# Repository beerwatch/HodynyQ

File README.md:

# HodynyQ
RP2040 to replace RPi Linux in my desktop alarm clock and enable functionality extension towards wearable watch

# Note about Google Oauth2 application identity key
The Oauth2/client_secret.json file contains Google Oauth2 application identity. It is used to present application information and security policies and for tracking application use. A personified access token is needed to actually access Google API. 
The access token is generated during process that involves actual person's log-in. The resulting access token file shall be uploaded as Oauth2/client_token.json.

For more information see https://developers.google.com/identity/protocols/oauth2. Because of limitations listed in https://developers.google.com/identity/protocols/oauth2/limited-input-device#allowedscopes I had to use https://developers.google.com/identity/protocols/oauth2/native-app. I don't really understand why there is such limitation when your application wants only to read calendar items as they can be shared to anybody by the user.

The application components around SGApi.py showcase minimal Micropython code to interact with Google Oauth2 that leaves some of RP2040 RAM free to run other tasks. Oops, I did it again!

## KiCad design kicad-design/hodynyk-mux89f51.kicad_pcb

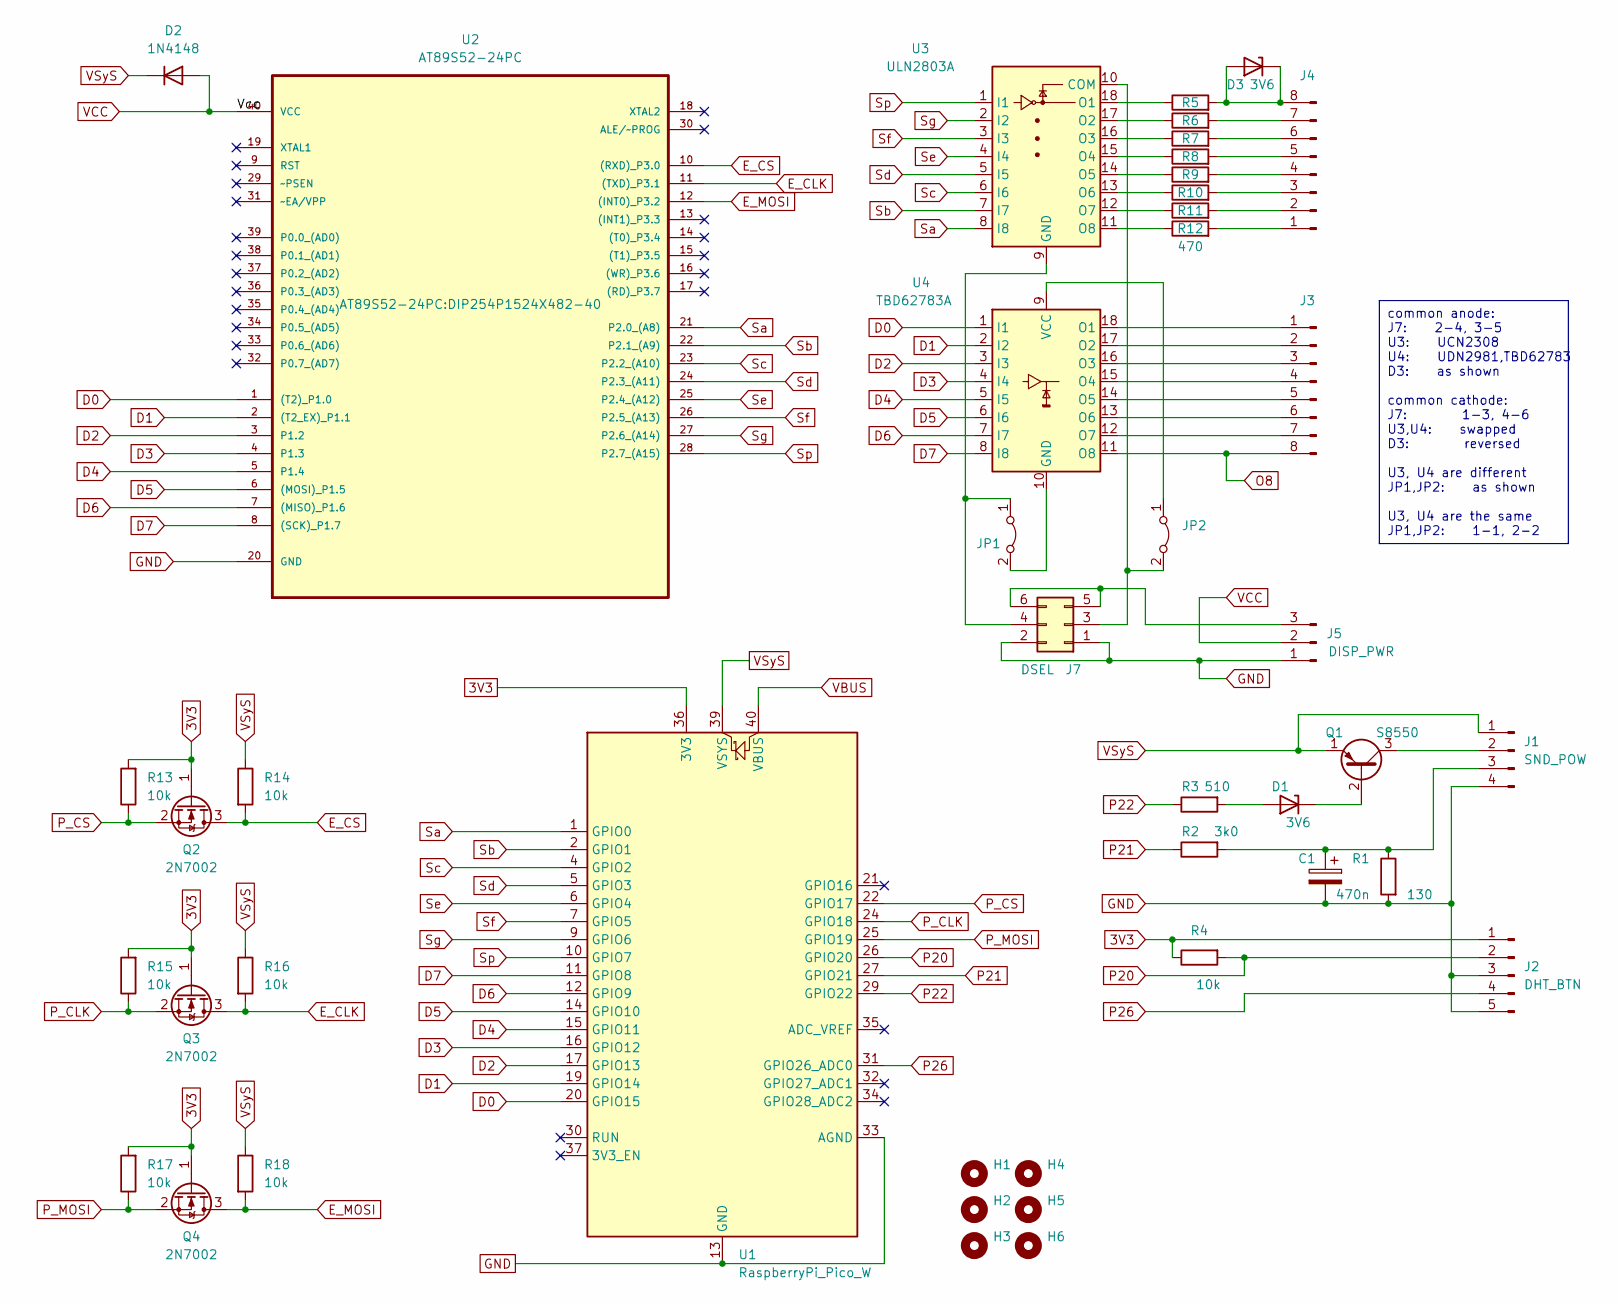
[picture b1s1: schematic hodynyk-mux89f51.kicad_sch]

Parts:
C1: 470n; CP_Radial_D4.0mm_P2.00mm
D1: 3V6; D_DO-35_SOD27_P7.62mm_Horizontal
D2: 1N4148; D_DO-35_SOD27_P7.62mm_Horizontal
D3: 3V6; D_DO-34_SOD68_P7.62mm_Horizontal
H1, H2, H3, H4, H5, H6: MountingHole_2.2mm_M2_ISO14580
J1: SND_POW; PinHeader_1x04_P2.54mm_Vertical
J2: DHT_BTN; PinHeader_1x05_P2.54mm_Vertical
J3: DISP_D; PinHeader_1x08_P2.54mm_Vertical
J4: DISP_S; PinHeader_1x08_P2.54mm_Vertical
J5: DISP_PWR; PinHeader_1x03_P2.54mm_Vertical
J7: DSEL; PinHeader_2x03_P2.54mm_Vertical
JP1, JP2: Jumper_2_Bridged; SolderJumper-2_P1.3mm_Bridged_Pad1.0x1.5mm
Q1: S8550; TO-92_HandSolder
Q2, Q3, Q4: 2N7002; SOT-23
R1: 130; R_Axial_DIN0204_L3.6mm_D1.6mm_P7.62mm_Horizontal
R2: 3k0; R_Axial_DIN0204_L3.6mm_D1.6mm_P7.62mm_Horizontal
R3: 510; R_Axial_DIN0204_L3.6mm_D1.6mm_P7.62mm_Horizontal
R4: 10k; R_Axial_DIN0204_L3.6mm_D1.6mm_P7.62mm_Horizontal
R5, R6, R7, R8, R9, R10, R11, R12: 470; R_Axial_DIN0204_L3.6mm_D1.6mm_P7.62mm_Horizontal
R13, R14, R15, R16, R17, R18: 10k; R_0603_1608Metric
U1: RaspberryPi_Pico_W; RaspberryPi_Pico_Common
U2: AT89S52-24PC; DIP254P1524X482-40; MPN AT89S52-24PC
U3: ULN2803A; DIP-18_W7.62mm_Socket_LongPads
U4: TBD62783A; DIP-18_W7.62mm_Socket_LongPads

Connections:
3V3: J2.1, Q2.1 (G), Q3.1 (G), Q4.1 (G), R4.1, R13.2, R15.2, R17.2, U1.36 (3V3)
D0: U1.20 (GPIO15), U2.1 ((T2)_P1.0), U4.1 (I1)
D1: U1.19 (GPIO14), U2.2 ((T2_EX)_P1.1), U4.2 (I2)
D2: U1.17 (GPIO13), U2.3 (P1.2), U4.3 (I3)
D3: U1.16 (GPIO12), U2.4 (P1.3), U4.4 (I4)
D4: U1.15 (GPIO11), U2.5 (P1.4), U4.5 (I5)
D5: U1.14 (GPIO10), U2.6 ((MOSI)_P1.5), U4.6 (I6)
D6: U1.12 (GPIO9), U2.7 ((MISO)_P1.6), U4.7 (I7)
D7: U1.11 (GPIO8), U2.8 ((SCK)_P1.7), U4.8 (I8)
E_CLK: Q3.3 (D), R16.2, U2.11 ((TXD)_P3.1)
E_CS: Q2.3 (D), R14.2, U2.10 ((RXD)_P3.0)
E_MOSI: Q4.3 (D), R18.2, U2.12 ((INT0)_P3.2)
GND: C1.2, J1.4, J2.3, J2.5, J5.1, J7.1, J7.2, R1.2, U1.3 (GND), U1.8 (GND), U1.13 (GND), U1.18 (GND), U1.23 (GND), U1.28 (GND), U1.33 (AGND), U1.38 (GND), U2.20 (GND)
unnamed: D1.2 (A), R3.2
unnamed: D1.1 (K), Q1.2 (B)
unnamed: D3.1 (K), D3.2 (A), J4.8, R5.2
unnamed: J1.2, Q1.3 (C)
unnamed: C1.1, J1.3, R1.1, R2.2
unnamed: J3.1, U4.18 (O1)
unnamed: J3.2, U4.17 (O2)
unnamed: J3.3, U4.16 (O3)
unnamed: J3.4, U4.15 (O4)
unnamed: J3.5, U4.14 (O5)
unnamed: J3.6, U4.13 (O6)
unnamed: J3.7, U4.12 (O7)
unnamed: J4.1, R12.2
unnamed: J4.2, R11.2
unnamed: J4.3, R10.2
unnamed: J4.4, R9.2
unnamed: J4.5, R8.2
unnamed: J4.6, R7.2
unnamed: J4.7, R6.2
unnamed: J5.3, J7.5, J7.6
unnamed: J7.3, JP2.2 (B), U3.10 (COM)
unnamed: J7.4, JP1.1 (A), U3.9 (GND)
unnamed: JP1.2 (B), U4.10 (GND)
unnamed: JP2.1 (A), U4.9 (VCC)
unnamed: R5.1, U3.18 (O1)
unnamed: R6.1, U3.17 (O2)
unnamed: R7.1, U3.16 (O3)
unnamed: R8.1, U3.15 (O4)
unnamed: R9.1, U3.14 (O5)
unnamed: R10.1, U3.13 (O6)
unnamed: R11.1, U3.12 (O7)
unnamed: R12.1, U3.11 (O8)
O8: J3.8, U4.11 (O8)
P20: J2.2, R4.2, U1.26 (GPIO20)
P21: R2.1, U1.27 (GPIO21)
P22: R3.1, U1.29 (GPIO22)
P26: J2.4, U1.31 (GPIO26_ADC0)
P_CLK: Q3.2 (S), R15.1, U1.24 (GPIO18)
P_CS: Q2.2 (S), R13.1, U1.22 (GPIO17)
P_MOSI: Q4.2 (S), R17.1, U1.25 (GPIO19)
Sa: U1.1 (GPIO0), U2.21 (P2.0_(A8)), U3.8 (I8)
Sb: U1.2 (GPIO1), U2.22 (P2.1_(A9)), U3.7 (I7)
Sc: U1.4 (GPIO2), U2.23 (P2.2_(A10)), U3.6 (I6)
Sd: U1.5 (GPIO3), U2.24 (P2.3_(A11)), U3.5 (I5)
Se: U1.6 (GPIO4), U2.25 (P2.4_(A12)), U3.4 (I4)
Sf: U1.7 (GPIO5), U2.26 (P2.5_(A13)), U3.3 (I3)
Sg: U1.9 (GPIO6), U2.27 (P2.6_(A14)), U3.2 (I2)
Sp: U1.10 (GPIO7), U2.28 (P2.7_(A15)), U3.1 (I1)
VBUS: U1.40 (VBUS)
VCC: D2.2 (A), J5.2, U2.40 (VCC)
VSyS: D2.1 (K), J1.1, Q1.1 (E), R14.1, R16.1, R18.1, U1.39 (VSYS)

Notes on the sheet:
common anode: J7: 2-4, 3-5 U3: UCN2308 U4: UDN2981,TBD62783 D3: as shown common cathode: J7: 1-3, 4-6 U3,U4: swapped D3: reversed U3, U4 are different JP1,JP2: as shown U3, U4 are the same JP1,JP2: 1-1, 2-2

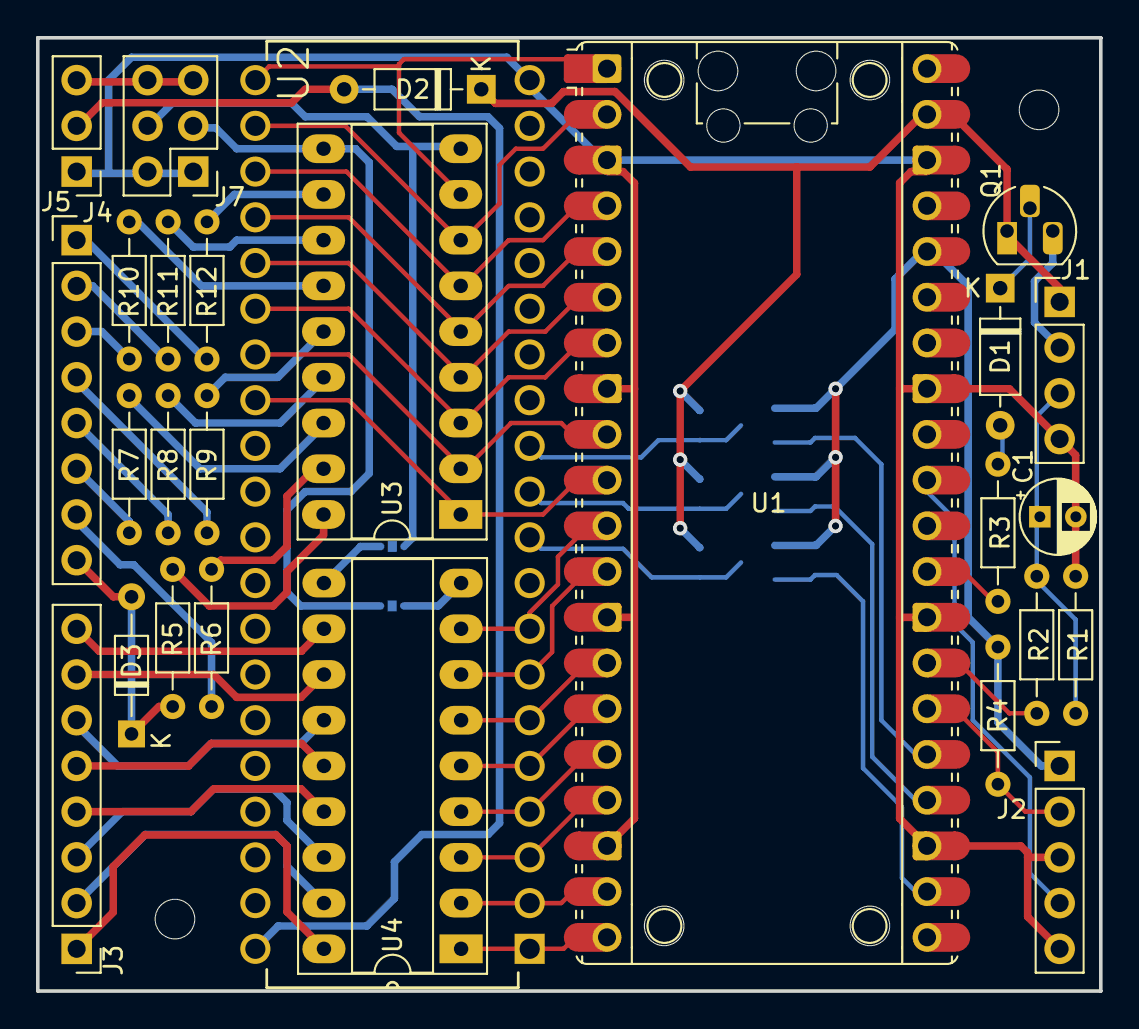
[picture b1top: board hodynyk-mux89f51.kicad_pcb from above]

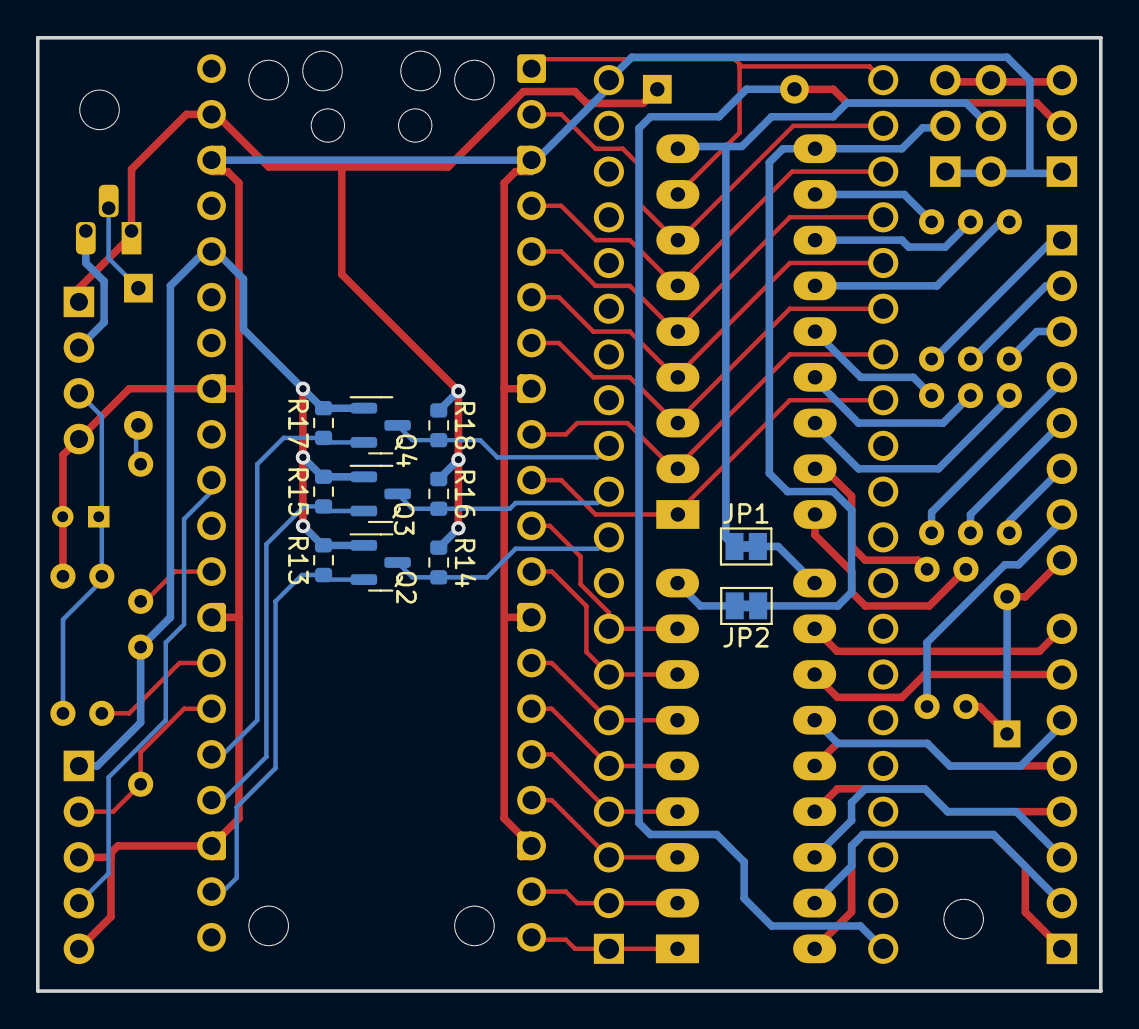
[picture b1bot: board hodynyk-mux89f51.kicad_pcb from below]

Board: 2 copper layers, 59.1 x 53.0 mm, 44 parts (11 on the bottom side), 63 nets.

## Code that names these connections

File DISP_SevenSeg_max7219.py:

from machine import Pin, SPI, Timer
from max7219 import SevenSegment, SEG_7219_STD

DAYS = ( 'Po', 'Ut', 'St', 'Ct', 'Pa', 'So', 'Ne', '__' )

class DISP_SevenSeg_max7219:
    def __init__( self , argv ):
        CS = Pin(   argv['P_CS']  , Pin.OUT)
        CLK = Pin(  argv['P_CLK'] )
        MOSI = Pin( argv['P_MOSI'] )
        spi = SPI(0, baudrate=500000,  sck = CLK, mosi = MOSI)
        self.display = SevenSegment(spi, CS, 4)
        self.display.init(0)
        self.display.buffer=[0,0,0,0]
        self.display.show()
        self.dimmer = Timer()
        self.setBright( argv[ 'BRIGHT' ] , -1 )

    def setBright( self, toBright, fromBright=None, transTime=0, repeat=False ):
        self.dimmer.deinit()
        if fromBright == None: fromBright = self.currBright
        self.delta = toBright - fromBright
        if self.delta == 0: return

        self.stepTime = 20
        if transTime < self.stepTime:
            self.currBright = toBright
        else:
            if abs(self.delta) * self.stepTime < transTime:
                self.stepTime = transTime // abs(self.delta)
            steps = transTime // self.stepTime
            self.delta = ( self.delta + 1 ) // ( steps if steps > 1 else 1 )
            if abs(self.delta) < 1:
                self.delta = 1 if toBright > fromBright else -1
            self.toBright   = toBright
            self.fromBright = fromBright
            self.repeat     = repeat
            self.currBright = fromBright + self.delta // 2
            self.dimmer.init( period = self.stepTime , mode=Timer.PERIODIC, callback=self._dimstep )
        self.display.brightness( self.currBright )

    def _dimstep( self, dimmer ):
        if abs( self.toBright - self.currBright ) > abs( self.delta ):
            self.currBright = self.currBright + self.delta
        else:
            self.currBright = self.toBright
            if self.repeat:
                self.delta, self.fromBright, self.toBright = -self.delta, self.toBright, self.fromBright
            else:
                self.dimmer.deinit()
        self.display.brightness( self.currBright )

    def showConnect( self, num ):
        self.display.buffer = [ SEG_7219_STD[ord('C')], SEG_7219_STD[ord('o')], SEG_7219_STD[ ord('n') + num // 10], SEG_7219_STD[num % 10] ]
        self.display.show()

    def showNTPGet( self ):
        self.display.buffer = [ SEG_7219_STD[ord('N')], SEG_7219_STD[ord('t')], SEG_7219_STD[ord('p')], 0 ]
        self.display.show()

    def showTime( self, t_struct, ddots ):
        if ddots & 4:
            self.display.buffer = [ 0, 0, 0, 0 ]
            if ddots & 1:
                self.display.buffer[ 0 if ddots & 2 else 1 ] |= 0x80
            else:
                self.display.buffer[ 2 ] |= 0x80
        else:
            self.display.buffer = [ SEG_7219_STD[t_struct[3] // 10], SEG_7219_STD[t_struct[3] % 10], SEG_7219_STD[t_struct[4] // 10], SEG_7219_STD[t_struct[4] % 10] ]
            if ddots & 1:
                self.display.buffer[ 0 if ddots & 2 else 1 ] |= 0x80
                self.display.buffer[ 2 ] |= 0x80
        self.display.show()

    def showAlmTime( self, tA_struct , tN_struct, td, ddots ):
        self.display.buffer = [ SEG_7219_STD[tA_struct[3] // 10], SEG_7219_STD[tA_struct[3] % 10], SEG_7219_STD[tA_struct[4] // 10], SEG_7219_STD[tA_struct[4] % 10] ]
        self.display.buffer[ 0 if ddots & 2 else 1 ] |= 0x80
        self.display.show()

    def showDate( self, t_struct, ddots ):
        dy = DAYS[ t_struct[6] ]
        tt = '{:02d}{:2d}{:4d}'.format( t_struct[2], t_struct[1], t_struct[0] )
        self.display.buffer = [ SEG_7219_STD[t_struct[2] // 10], SEG_7219_STD[t_struct[2] % 10], SEG_7219_STD[t_struct[1] // 10], SEG_7219_STD[t_struct[1] % 10] ]
        self.display.buffer[ 0 if ddots & 2 else 1 ] |= 0x80
        self.display.show()

    def showEnv( self, ddots , sensData ):
        dd = '{:2d}C {:2d}%'.format( sensData[0], sensData[1] )
        self.display.buffer = [ SEG_7219_STD[sensData[0] // 10] , SEG_7219_STD[sensData[0] % 10] , 0x63, SEG_7219_STD[ord('[')] ]
        self.display.show()

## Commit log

2024-01-02 Add files via upload
    Initial public version.
    TODO: add web UI and provide workflow for obtaining access token of type "installed" because of Google "device"-type access token policies.
2024-01-03 Update README.md
    Prevent future warnings about exposed Google Oauth2 keys.
2024-01-03 Update README.md
    Be more specific about Google Oauth2
2024-01-03 Update README.md
    Typo
2024-01-03 Add schematics and hardware design files
2024-01-05 Fixed expired alarm logic in controller
